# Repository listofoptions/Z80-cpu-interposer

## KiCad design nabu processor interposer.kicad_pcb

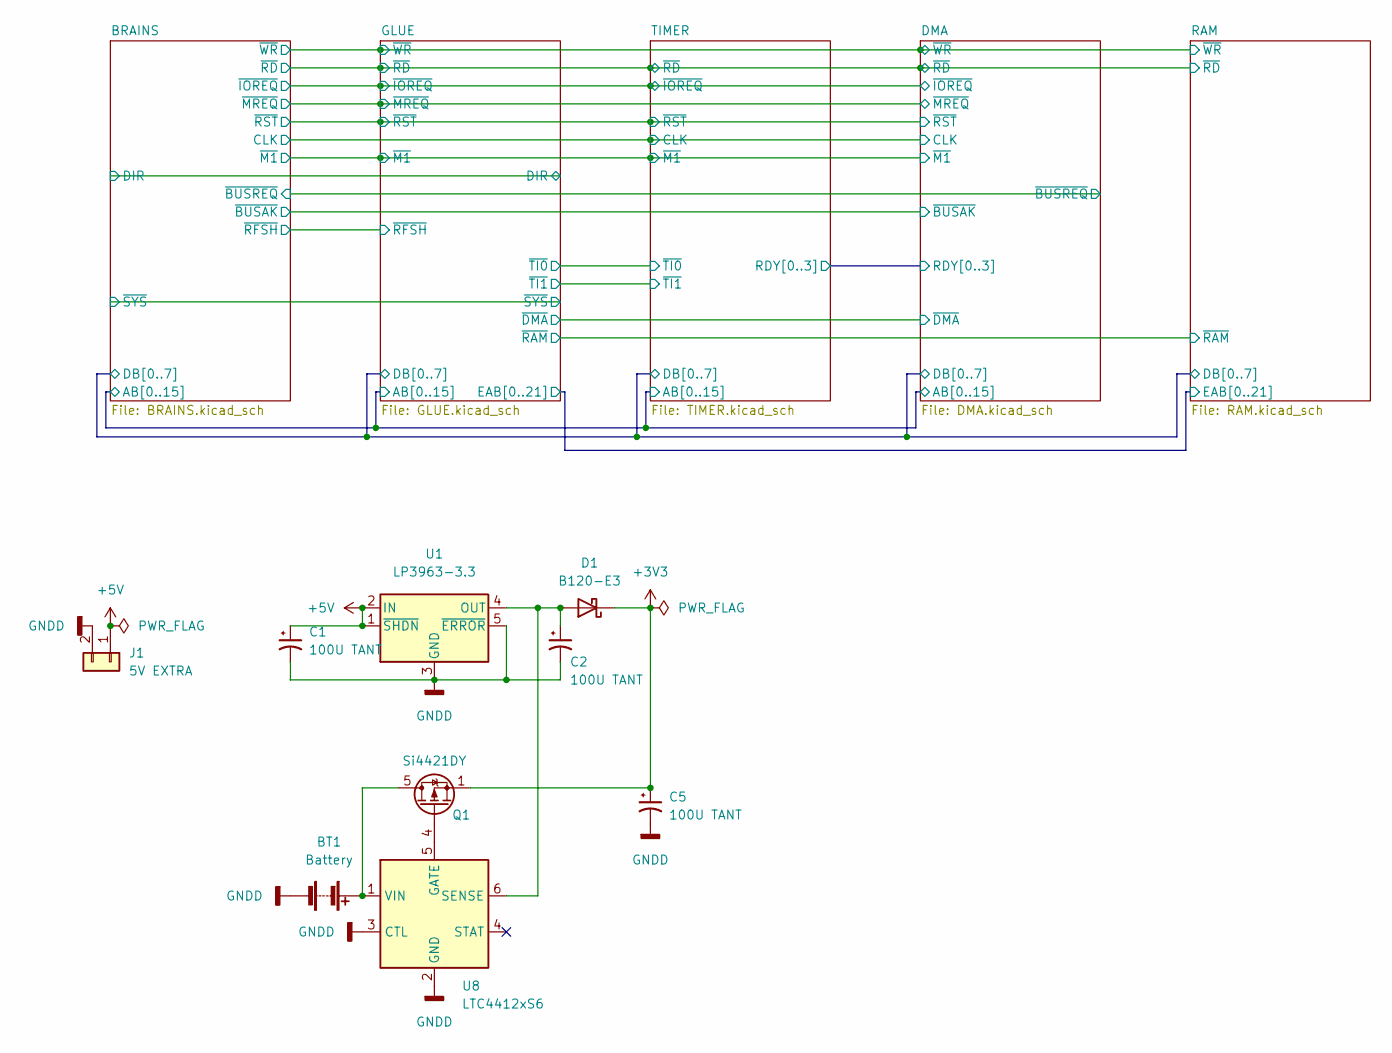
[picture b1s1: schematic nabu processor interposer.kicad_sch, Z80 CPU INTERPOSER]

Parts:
BT1: Battery; BatteryHolder_Keystone_2462_2xAA
C1, C2, C5: 100U TANT; CP_EIA-3528-15_AVX-H
D1: B120-E3; D_SMA
J1: 5V EXTRA; PinHeader_1x02_P2.54mm_Vertical
Q1: Si4421DY; SO-8_3.9x4.9mm_P1.27mm
U1: LP3963-3.3; TO-263-5_TabPin3
U8: LTC4412xS6; TSOT-23-6

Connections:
+3V3: C5.1, D1.1 (K), Q1.1 (S), Q1.2, Q1.3; also elsewhere on the board
+5V: C1.1, J1.1, U1.1 (~SHDN), U1.2 (IN); also elsewhere on the board
GND: BT1.2 (-), C1.2, C2.2, C5.2, J1.2, U1.3 (GND), U1.5 (~ERROR), U8.2 (GND), U8.3 (CTL); also elsewhere on the board
unnamed: BT1.1 (+), Q1.5 (D), Q1.6, Q1.7, Q1.8, U8.1 (VIN)
unnamed: C2.1, D1.2 (A), U1.4 (OUT), U8.6 (SENSE)
unnamed: Q1.4 (G), U8.5 (GATE)

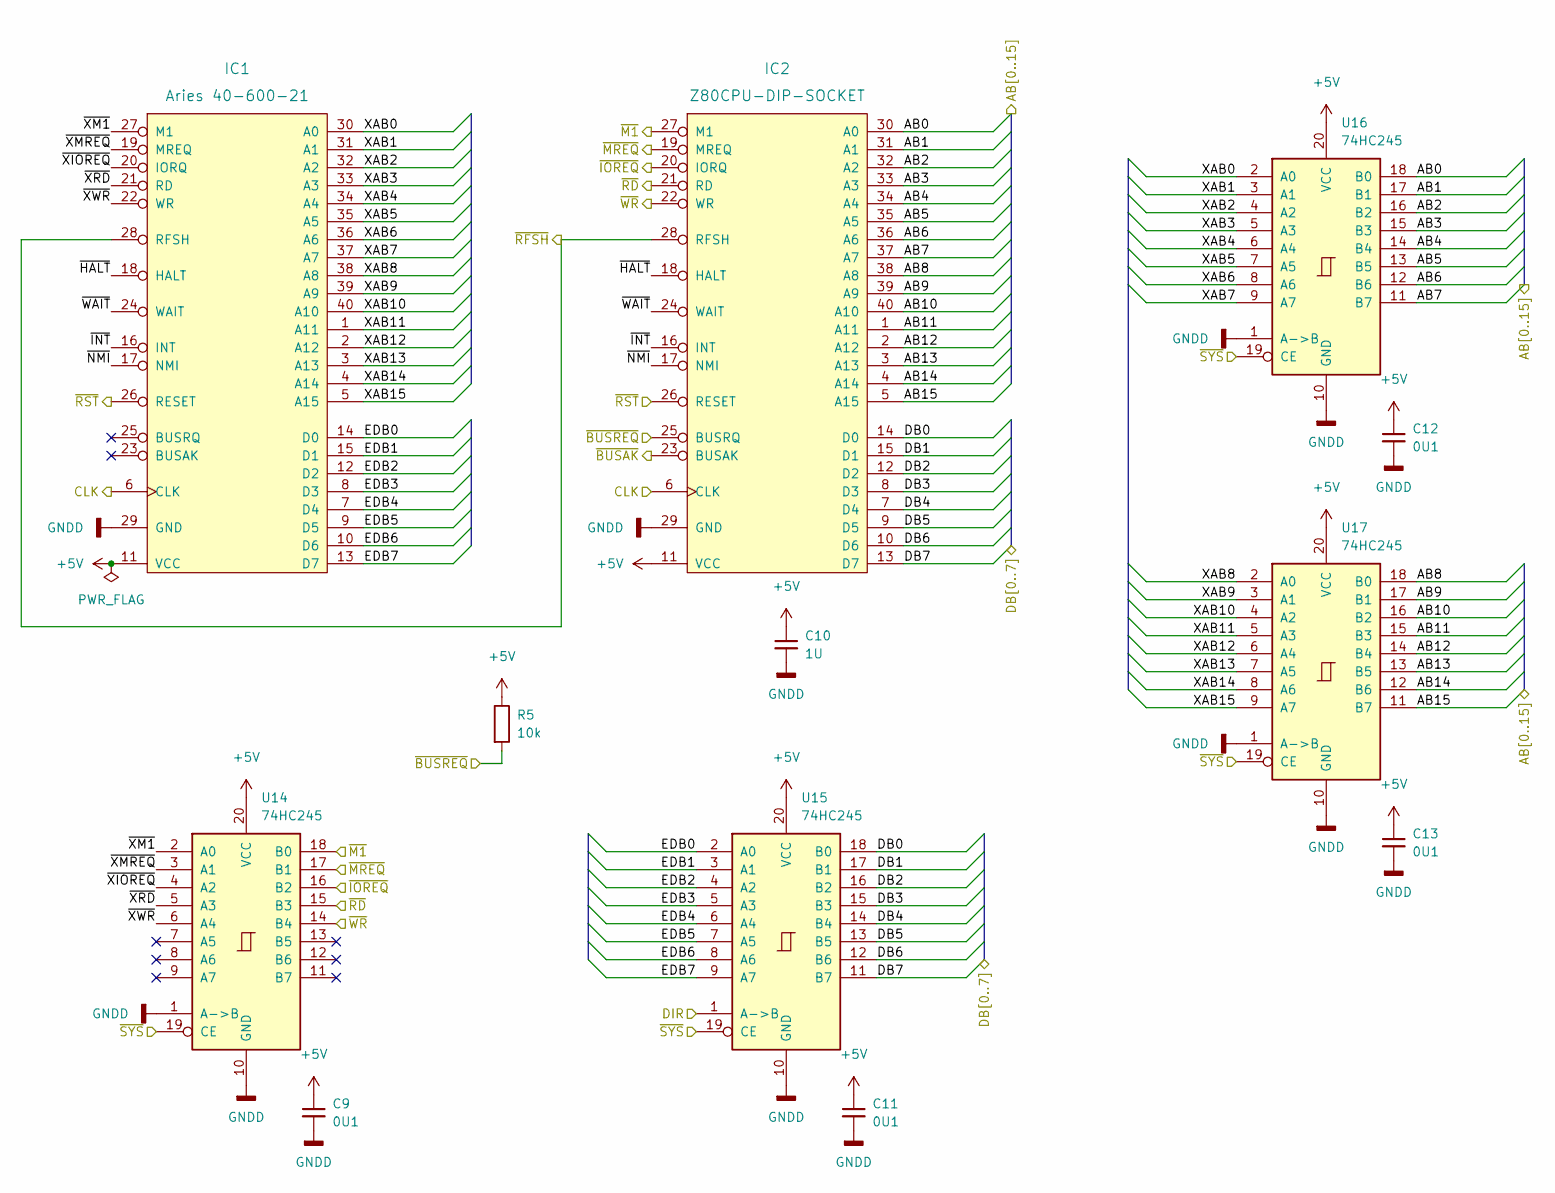
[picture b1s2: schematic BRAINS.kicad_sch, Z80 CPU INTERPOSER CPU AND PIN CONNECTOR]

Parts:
C9, C11, C12, C13: 0U1; C_1206_3216Metric
C10: 1U; C_1206_3216Metric
IC1: Aries 40-600-21; DIP-40_W15.24mm_Socket
IC2: Z80CPU-DIP-SOCKET; DIP-40_W15.24mm_Socket
R5: 10k; R_0603_1608Metric
U14, U15, U16, U17: 74HC245; TSSOP-20_4.4x6.5mm_P0.65mm

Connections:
+5V: C9.1, C10.1, C11.1, C12.1, C13.1, IC1.11 (VCC), IC2.11 (VCC), R5.1, U14.20 (VCC), U15.20 (VCC), U16.20 (VCC), U17.20 (VCC); also elsewhere on the board
/BRAINS/AB0: IC2.30 (A0), U16.18 (B0); also elsewhere on the board
/BRAINS/AB1: IC2.31 (A1), U16.17 (B1); also elsewhere on the board
/BRAINS/AB2: IC2.32 (A2), U16.16 (B2); also elsewhere on the board
/BRAINS/AB3: IC2.33 (A3), U16.15 (B3); also elsewhere on the board
/BRAINS/AB4: IC2.34 (A4), U16.14 (B4); also elsewhere on the board
/BRAINS/AB5: IC2.35 (A5), U16.13 (B5); also elsewhere on the board
/BRAINS/AB6: IC2.36 (A6), U16.12 (B6); also elsewhere on the board
/BRAINS/AB7: IC2.37 (A7), U16.11 (B7); also elsewhere on the board
/BRAINS/AB8: IC2.38 (A8), U17.18 (B0); also elsewhere on the board
/BRAINS/AB9: IC2.39 (A9), U17.17 (B1); also elsewhere on the board
/BRAINS/AB10: IC2.40 (A10), U17.16 (B2); also elsewhere on the board
/BRAINS/AB11: IC2.1 (A11), U17.15 (B3); also elsewhere on the board
/BRAINS/AB12: IC2.2 (A12), U17.14 (B4); also elsewhere on the board
/BRAINS/AB13: IC2.3 (A13), U17.13 (B5); also elsewhere on the board
/BRAINS/AB14: IC2.4 (A14), U17.12 (B6); also elsewhere on the board
/BRAINS/AB15: IC2.5 (A15), U17.11 (B7); also elsewhere on the board
/BRAINS/CLK: IC1.6 (CLK), IC2.6 (CLK); also elsewhere on the board
/BRAINS/DB0: IC2.14 (D0), U15.18 (B0); also elsewhere on the board
/BRAINS/DB1: IC2.15 (D1), U15.17 (B1); also elsewhere on the board
/BRAINS/DB2: IC2.12 (D2), U15.16 (B2); also elsewhere on the board
/BRAINS/DB3: IC2.8 (D3), U15.15 (B3); also elsewhere on the board
/BRAINS/DB4: IC2.7 (D4), U15.14 (B4); also elsewhere on the board
/BRAINS/DB5: IC2.9 (D5), U15.13 (B5); also elsewhere on the board
/BRAINS/DB6: IC2.10 (D6), U15.12 (B6); also elsewhere on the board
/BRAINS/DB7: IC2.13 (D7), U15.11 (B7); also elsewhere on the board
/BRAINS/DIR: U15.1 (A->B); also elsewhere on the board
/BRAINS/EDB0: IC1.14 (D0), U15.2 (A0)
/BRAINS/EDB1: IC1.15 (D1), U15.3 (A1)
/BRAINS/EDB2: IC1.12 (D2), U15.4 (A2)
/BRAINS/EDB3: IC1.8 (D3), U15.5 (A3)
/BRAINS/EDB4: IC1.7 (D4), U15.6 (A4)
/BRAINS/EDB5: IC1.9 (D5), U15.7 (A5)
/BRAINS/EDB6: IC1.10 (D6), U15.8 (A6)
/BRAINS/EDB7: IC1.13 (D7), U15.9 (A7)
/BRAINS/XAB0: IC1.30 (A0), U16.2 (A0)
/BRAINS/XAB1: IC1.31 (A1), U16.3 (A1)
/BRAINS/XAB2: IC1.32 (A2), U16.4 (A2)
/BRAINS/XAB3: IC1.33 (A3), U16.5 (A3)
/BRAINS/XAB4: IC1.34 (A4), U16.6 (A4)
/BRAINS/XAB5: IC1.35 (A5), U16.7 (A5)
/BRAINS/XAB6: IC1.36 (A6), U16.8 (A6)
/BRAINS/XAB7: IC1.37 (A7), U16.9 (A7)
/BRAINS/XAB8: IC1.38 (A8), U17.2 (A0)
/BRAINS/XAB9: IC1.39 (A9), U17.3 (A1)
/BRAINS/XAB10: IC1.40 (A10), U17.4 (A2)
/BRAINS/XAB11: IC1.1 (A11), U17.5 (A3)
/BRAINS/XAB12: IC1.2 (A12), U17.6 (A4)
/BRAINS/XAB13: IC1.3 (A13), U17.7 (A5)
/BRAINS/XAB14: IC1.4 (A14), U17.8 (A6)
/BRAINS/XAB15: IC1.5 (A15), U17.9 (A7)
/BRAINS/~BUSAK: IC2.23 (BUSAK); also elsewhere on the board
/BRAINS/~BUSREQ: IC2.25 (BUSRQ), R5.2; also elsewhere on the board
/BRAINS/~HALT: IC1.18 (HALT), IC2.18 (HALT)
/BRAINS/~INT: IC1.16 (INT), IC2.16 (INT)
/BRAINS/~IOREQ: IC2.20 (IORQ), U14.16 (B2); also elsewhere on the board
/BRAINS/~M1: IC2.27 (M1), U14.18 (B0); also elsewhere on the board
/BRAINS/~MREQ: IC2.19 (MREQ), U14.17 (B1); also elsewhere on the board
/BRAINS/~NMI: IC1.17 (NMI), IC2.17 (NMI)
/BRAINS/~RD: IC2.21 (RD), U14.15 (B3); also elsewhere on the board
/BRAINS/~RFSH: IC1.28 (RFSH), IC2.28 (RFSH); also elsewhere on the board
/BRAINS/~RST: IC1.26 (RESET), IC2.26 (RESET); also elsewhere on the board
/BRAINS/~SYS: U14.19 (CE), U15.19 (CE), U16.19 (CE), U17.19 (CE); also elsewhere on the board
/BRAINS/~WAIT: IC1.24 (WAIT), IC2.24 (WAIT)
/BRAINS/~WR: IC2.22 (WR), U14.14 (B4); also elsewhere on the board
/BRAINS/~XIOREQ: IC1.20 (IORQ), U14.4 (A2)
/BRAINS/~XM1: IC1.27 (M1), U14.2 (A0)
/BRAINS/~XMREQ: IC1.19 (MREQ), U14.3 (A1)
/BRAINS/~XRD: IC1.21 (RD), U14.5 (A3)
/BRAINS/~XWR: IC1.22 (WR), U14.6 (A4)
GND: C9.2, C10.2, C11.2, C12.2, C13.2, IC1.29 (GND), IC2.29 (GND), U14.1 (A->B), U14.10 (GND), U15.10 (GND), U16.1 (A->B), U16.10 (GND), U17.1 (A->B), U17.10 (GND); also elsewhere on the board

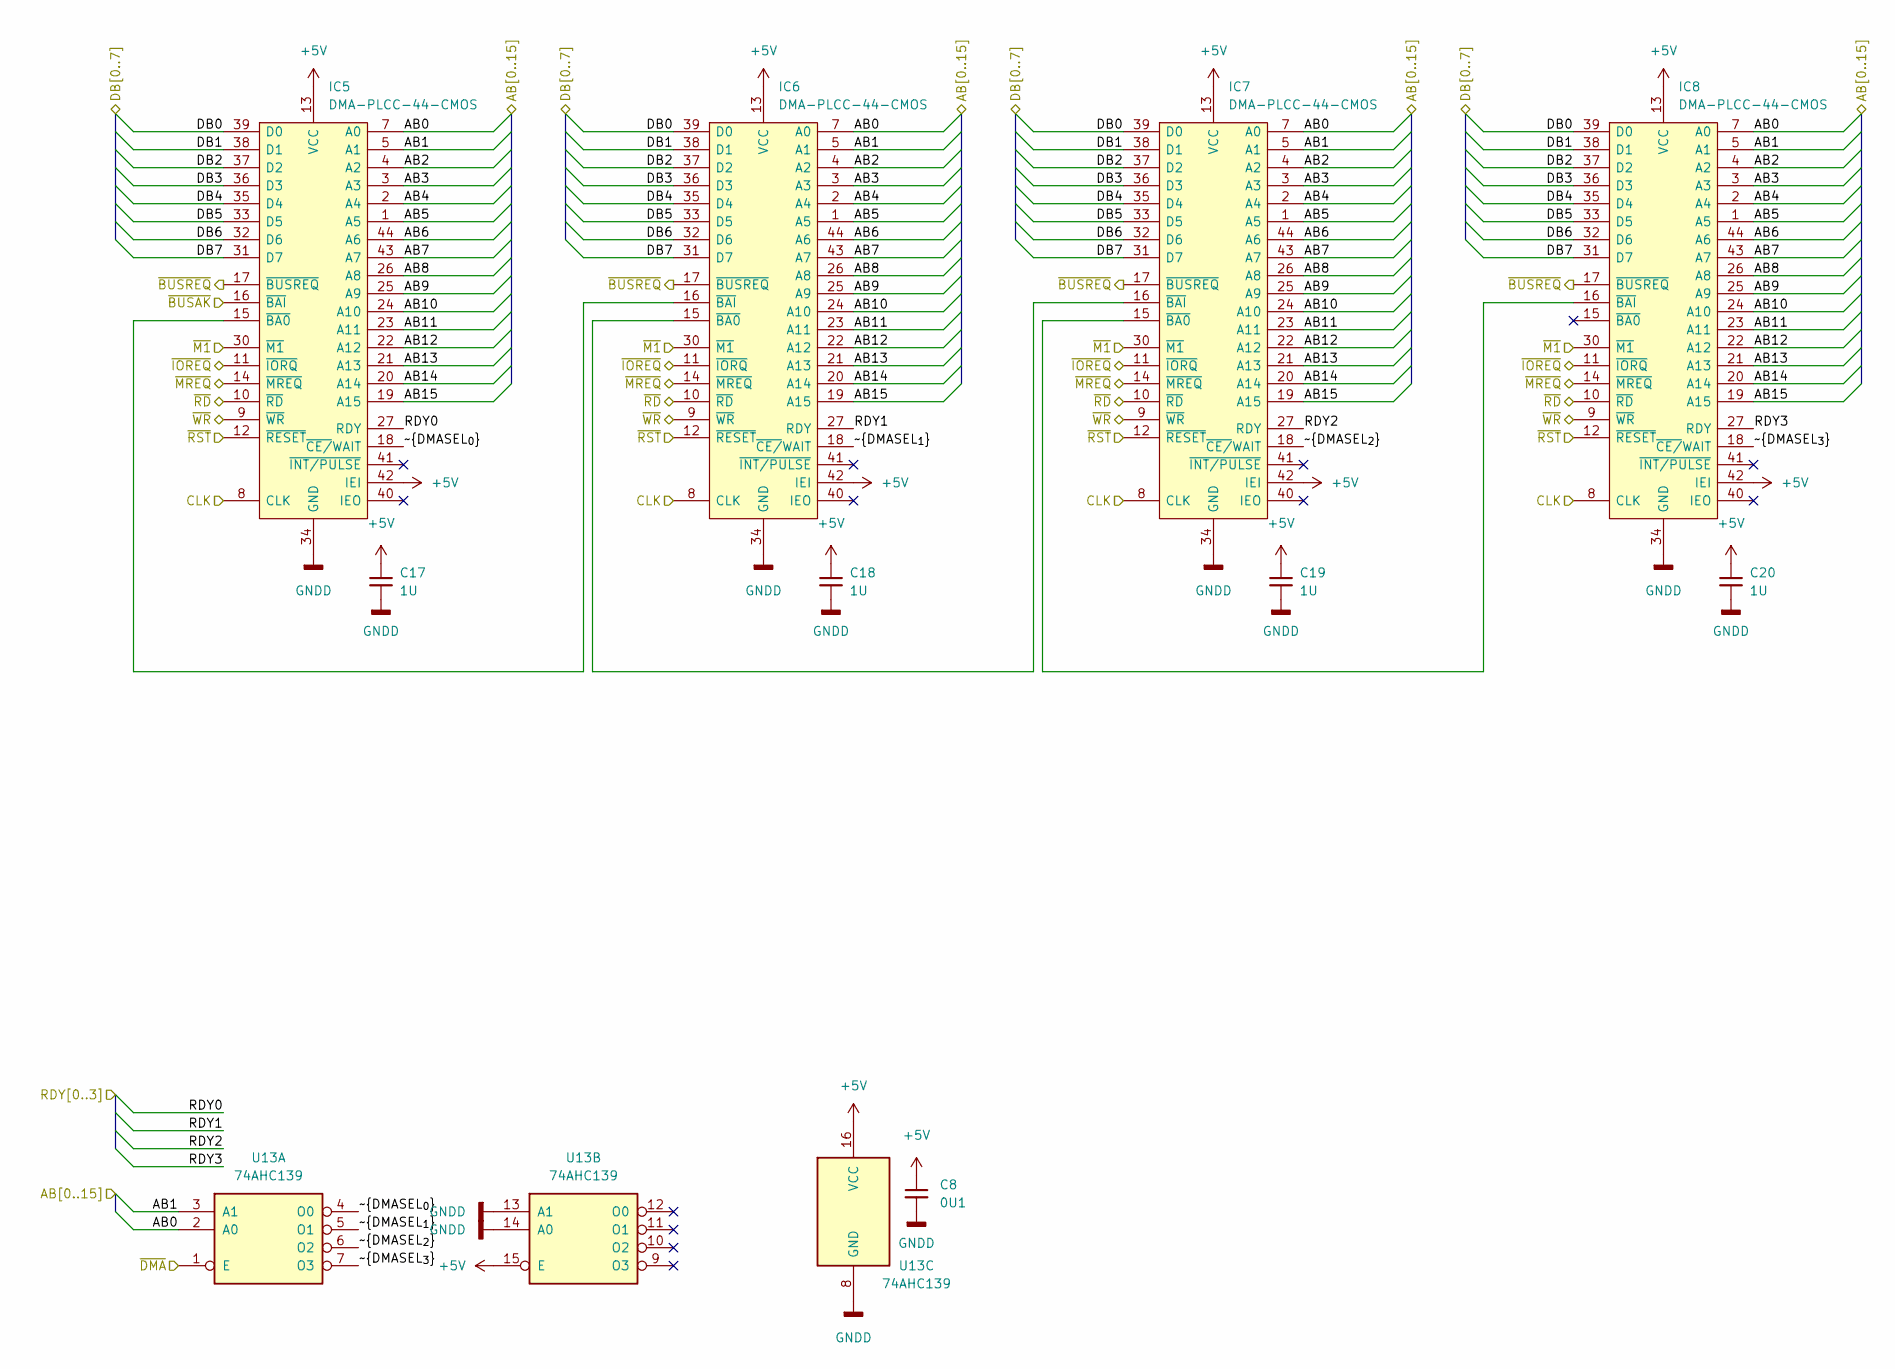
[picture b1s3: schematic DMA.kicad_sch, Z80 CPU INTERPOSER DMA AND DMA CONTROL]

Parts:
C8: 0U1; C_0603_1608Metric
C17, C18, C19, C20: 1U; C_1206_3216Metric
IC5, IC6, IC7, IC8: DMA-PLCC-44-CMOS; LQFP-44_10x10mm_P0.8mm; Manufacturer_Part_Number Z84C4206PEG; Mouser Part Number 692-Z84C4206PEG
U13: 74AHC139; TSSOP-16_4.4x5mm_P0.65mm

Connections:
+5V: C8.1, C17.1, C18.1, C19.1, C20.1, IC5.13 (VCC), IC5.42 (IEI), IC6.13 (VCC), IC6.42 (IEI), IC7.13 (VCC), IC7.42 (IEI), IC8.13 (VCC), IC8.42 (IEI), U13.15 (E), U13.16 (VCC); also elsewhere on the board
/BRAINS/AB0: IC5.7 (A0), IC6.7 (A0), IC7.7 (A0), IC8.7 (A0), U13.2 (A0); also elsewhere on the board
/BRAINS/AB1: IC5.5 (A1), IC6.5 (A1), IC7.5 (A1), IC8.5 (A1), U13.3 (A1); also elsewhere on the board
/BRAINS/AB2: IC5.4 (A2), IC6.4 (A2), IC7.4 (A2), IC8.4 (A2); also elsewhere on the board
/BRAINS/AB3: IC5.3 (A3), IC6.3 (A3), IC7.3 (A3), IC8.3 (A3); also elsewhere on the board
/BRAINS/AB4: IC5.2 (A4), IC6.2 (A4), IC7.2 (A4), IC8.2 (A4); also elsewhere on the board
/BRAINS/AB5: IC5.1 (A5), IC6.1 (A5), IC7.1 (A5), IC8.1 (A5); also elsewhere on the board
/BRAINS/AB6: IC5.44 (A6), IC6.44 (A6), IC7.44 (A6), IC8.44 (A6); also elsewhere on the board
/BRAINS/AB7: IC5.43 (A7), IC6.43 (A7), IC7.43 (A7), IC8.43 (A7); also elsewhere on the board
/BRAINS/AB8: IC5.26 (A8), IC6.26 (A8), IC7.26 (A8), IC8.26 (A8); also elsewhere on the board
/BRAINS/AB9: IC5.25 (A9), IC6.25 (A9), IC7.25 (A9), IC8.25 (A9); also elsewhere on the board
/BRAINS/AB10: IC5.24 (A10), IC6.24 (A10), IC7.24 (A10), IC8.24 (A10); also elsewhere on the board
/BRAINS/AB11: IC5.23 (A11), IC6.23 (A11), IC7.23 (A11), IC8.23 (A11); also elsewhere on the board
/BRAINS/AB12: IC5.22 (A12), IC6.22 (A12), IC7.22 (A12), IC8.22 (A12); also elsewhere on the board
/BRAINS/AB13: IC5.21 (A13), IC6.21 (A13), IC7.21 (A13), IC8.21 (A13); also elsewhere on the board
/BRAINS/AB14: IC5.20 (A14), IC6.20 (A14), IC7.20 (A14), IC8.20 (A14); also elsewhere on the board
/BRAINS/AB15: IC5.19 (A15), IC6.19 (A15), IC7.19 (A15), IC8.19 (A15); also elsewhere on the board
/BRAINS/CLK: IC5.8 (CLK), IC6.8 (CLK), IC7.8 (CLK), IC8.8 (CLK); also elsewhere on the board
/BRAINS/DB0: IC5.39 (D0), IC6.39 (D0), IC7.39 (D0), IC8.39 (D0); also elsewhere on the board
/BRAINS/DB1: IC5.38 (D1), IC6.38 (D1), IC7.38 (D1), IC8.38 (D1); also elsewhere on the board
/BRAINS/DB2: IC5.37 (D2), IC6.37 (D2), IC7.37 (D2), IC8.37 (D2); also elsewhere on the board
/BRAINS/DB3: IC5.36 (D3), IC6.36 (D3), IC7.36 (D3), IC8.36 (D3); also elsewhere on the board
/BRAINS/DB4: IC5.35 (D4), IC6.35 (D4), IC7.35 (D4), IC8.35 (D4); also elsewhere on the board
/BRAINS/DB5: IC5.33 (D5), IC6.33 (D5), IC7.33 (D5), IC8.33 (D5); also elsewhere on the board
/BRAINS/DB6: IC5.32 (D6), IC6.32 (D6), IC7.32 (D6), IC8.32 (D6); also elsewhere on the board
/BRAINS/DB7: IC5.31 (D7), IC6.31 (D7), IC7.31 (D7), IC8.31 (D7); also elsewhere on the board
/BRAINS/~BUSAK: IC5.16 (~BAI); also elsewhere on the board
/BRAINS/~BUSREQ: IC5.17 (~BUSREQ), IC6.17 (~BUSREQ), IC7.17 (~BUSREQ), IC8.17 (~BUSREQ); also elsewhere on the board
/BRAINS/~IOREQ: IC5.11 (~IORQ), IC6.11 (~IORQ), IC7.11 (~IORQ), IC8.11 (~IORQ); also elsewhere on the board
/BRAINS/~M1: IC5.30 (~M1), IC6.30 (~M1), IC7.30 (~M1), IC8.30 (~M1); also elsewhere on the board
/BRAINS/~MREQ: IC5.14 (~MREQ), IC6.14 (~MREQ), IC7.14 (~MREQ), IC8.14 (~MREQ); also elsewhere on the board
/BRAINS/~RD: IC5.10 (~RD), IC6.10 (~RD), IC7.10 (~RD), IC8.10 (~RD); also elsewhere on the board
/BRAINS/~RST: IC5.12 (~RESET), IC6.12 (~RESET), IC7.12 (~RESET), IC8.12 (~RESET); also elsewhere on the board
/BRAINS/~WR: IC5.9 (~WR), IC6.9 (~WR), IC7.9 (~WR), IC8.9 (~WR); also elsewhere on the board
/DMA/RDY0: IC5.27 (RDY); also elsewhere on the board
/DMA/RDY1: IC6.27 (RDY); also elsewhere on the board
/DMA/RDY2: IC7.27 (RDY); also elsewhere on the board
/DMA/RDY3: IC8.27 (RDY); also elsewhere on the board
/DMA/~DMASEL_{0}: IC5.18 (~CE/WAIT), U13.4 (O0)
/DMA/~DMASEL_{1}: IC6.18 (~CE/WAIT), U13.5 (O1)
/DMA/~DMASEL_{2}: IC7.18 (~CE/WAIT), U13.6 (O2)
/DMA/~DMASEL_{3}: IC8.18 (~CE/WAIT), U13.7 (O3)
/DMA/~DMA: U13.1 (E); also elsewhere on the board
GND: C8.2, C17.2, C18.2, C19.2, C20.2, IC5.34 (GND), IC6.34 (GND), IC7.34 (GND), IC8.34 (GND), U13.8 (GND), U13.13 (A1), U13.14 (A0); also elsewhere on the board
unnamed: IC5.15 (~BA0), IC6.16 (~BAI)
unnamed: IC6.15 (~BA0), IC7.16 (~BAI)
unnamed: IC7.15 (~BA0), IC8.16 (~BAI)

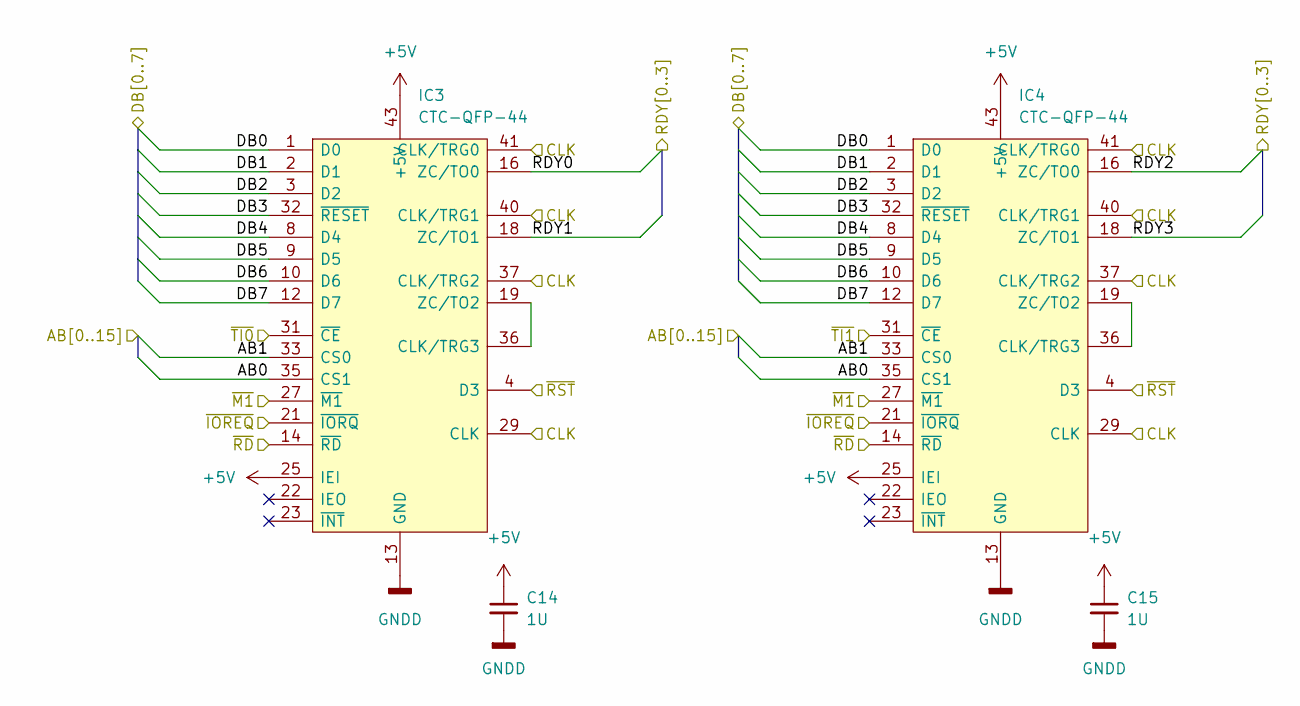
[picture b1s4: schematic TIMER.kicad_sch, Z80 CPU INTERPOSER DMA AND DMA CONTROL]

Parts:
C14, C15: 1U; C_1206_3216Metric
IC3, IC4: CTC-QFP-44; LQFP-44_10x10mm_P0.8mm; Manufacturer_Part_Number Z84C3010PEG; Mouser Part Number 692-Z84C3010PEG

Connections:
+5V: C14.1, C15.1, IC3.25 (IEI), IC3.43 (+5V), IC4.25 (IEI), IC4.43 (+5V); also elsewhere on the board
/BRAINS/AB0: IC3.35 (CS1), IC4.35 (CS1); also elsewhere on the board
/BRAINS/AB1: IC3.33 (CS0), IC4.33 (CS0); also elsewhere on the board
/BRAINS/CLK: IC3.29 (CLK), IC3.37 (CLK/TRG2), IC3.40 (CLK/TRG1), IC3.41 (CLK/TRG0), IC4.29 (CLK), IC4.37 (CLK/TRG2), IC4.40 (CLK/TRG1), IC4.41 (CLK/TRG0); also elsewhere on the board
/BRAINS/DB0: IC3.1 (D0), IC4.1 (D0); also elsewhere on the board
/BRAINS/DB1: IC3.2 (D1), IC4.2 (D1); also elsewhere on the board
/BRAINS/DB2: IC3.3 (D2), IC4.3 (D2); also elsewhere on the board
/BRAINS/DB3: IC3.32 (~RESET), IC4.32 (~RESET); also elsewhere on the board
/BRAINS/DB4: IC3.8 (D4), IC4.8 (D4); also elsewhere on the board
/BRAINS/DB5: IC3.9 (D5), IC4.9 (D5); also elsewhere on the board
/BRAINS/DB6: IC3.10 (D6), IC4.10 (D6); also elsewhere on the board
/BRAINS/DB7: IC3.12 (D7), IC4.12 (D7); also elsewhere on the board
/BRAINS/~IOREQ: IC3.21 (~IORQ), IC4.21 (~IORQ); also elsewhere on the board
/BRAINS/~M1: IC3.27 (~M1), IC4.27 (~M1); also elsewhere on the board
/BRAINS/~RD: IC3.14 (~RD), IC4.14 (~RD); also elsewhere on the board
/BRAINS/~RST: IC3.4 (D3), IC4.4 (D3); also elsewhere on the board
/DMA/RDY0: IC3.16 (ZC/TO0); also elsewhere on the board
/DMA/RDY1: IC3.18 (ZC/TO1); also elsewhere on the board
/DMA/RDY2: IC4.16 (ZC/TO0); also elsewhere on the board
/DMA/RDY3: IC4.18 (ZC/TO1); also elsewhere on the board
/GLUE/~TI0: IC3.31 (~CE); also elsewhere on the board
/GLUE/~TI1: IC4.31 (~CE); also elsewhere on the board
GND: C14.2, C15.2, IC3.13 (GND), IC4.13 (GND); also elsewhere on the board
unnamed: IC3.19 (ZC/TO2), IC3.36 (CLK/TRG3)
unnamed: IC4.19 (ZC/TO2), IC4.36 (CLK/TRG3)

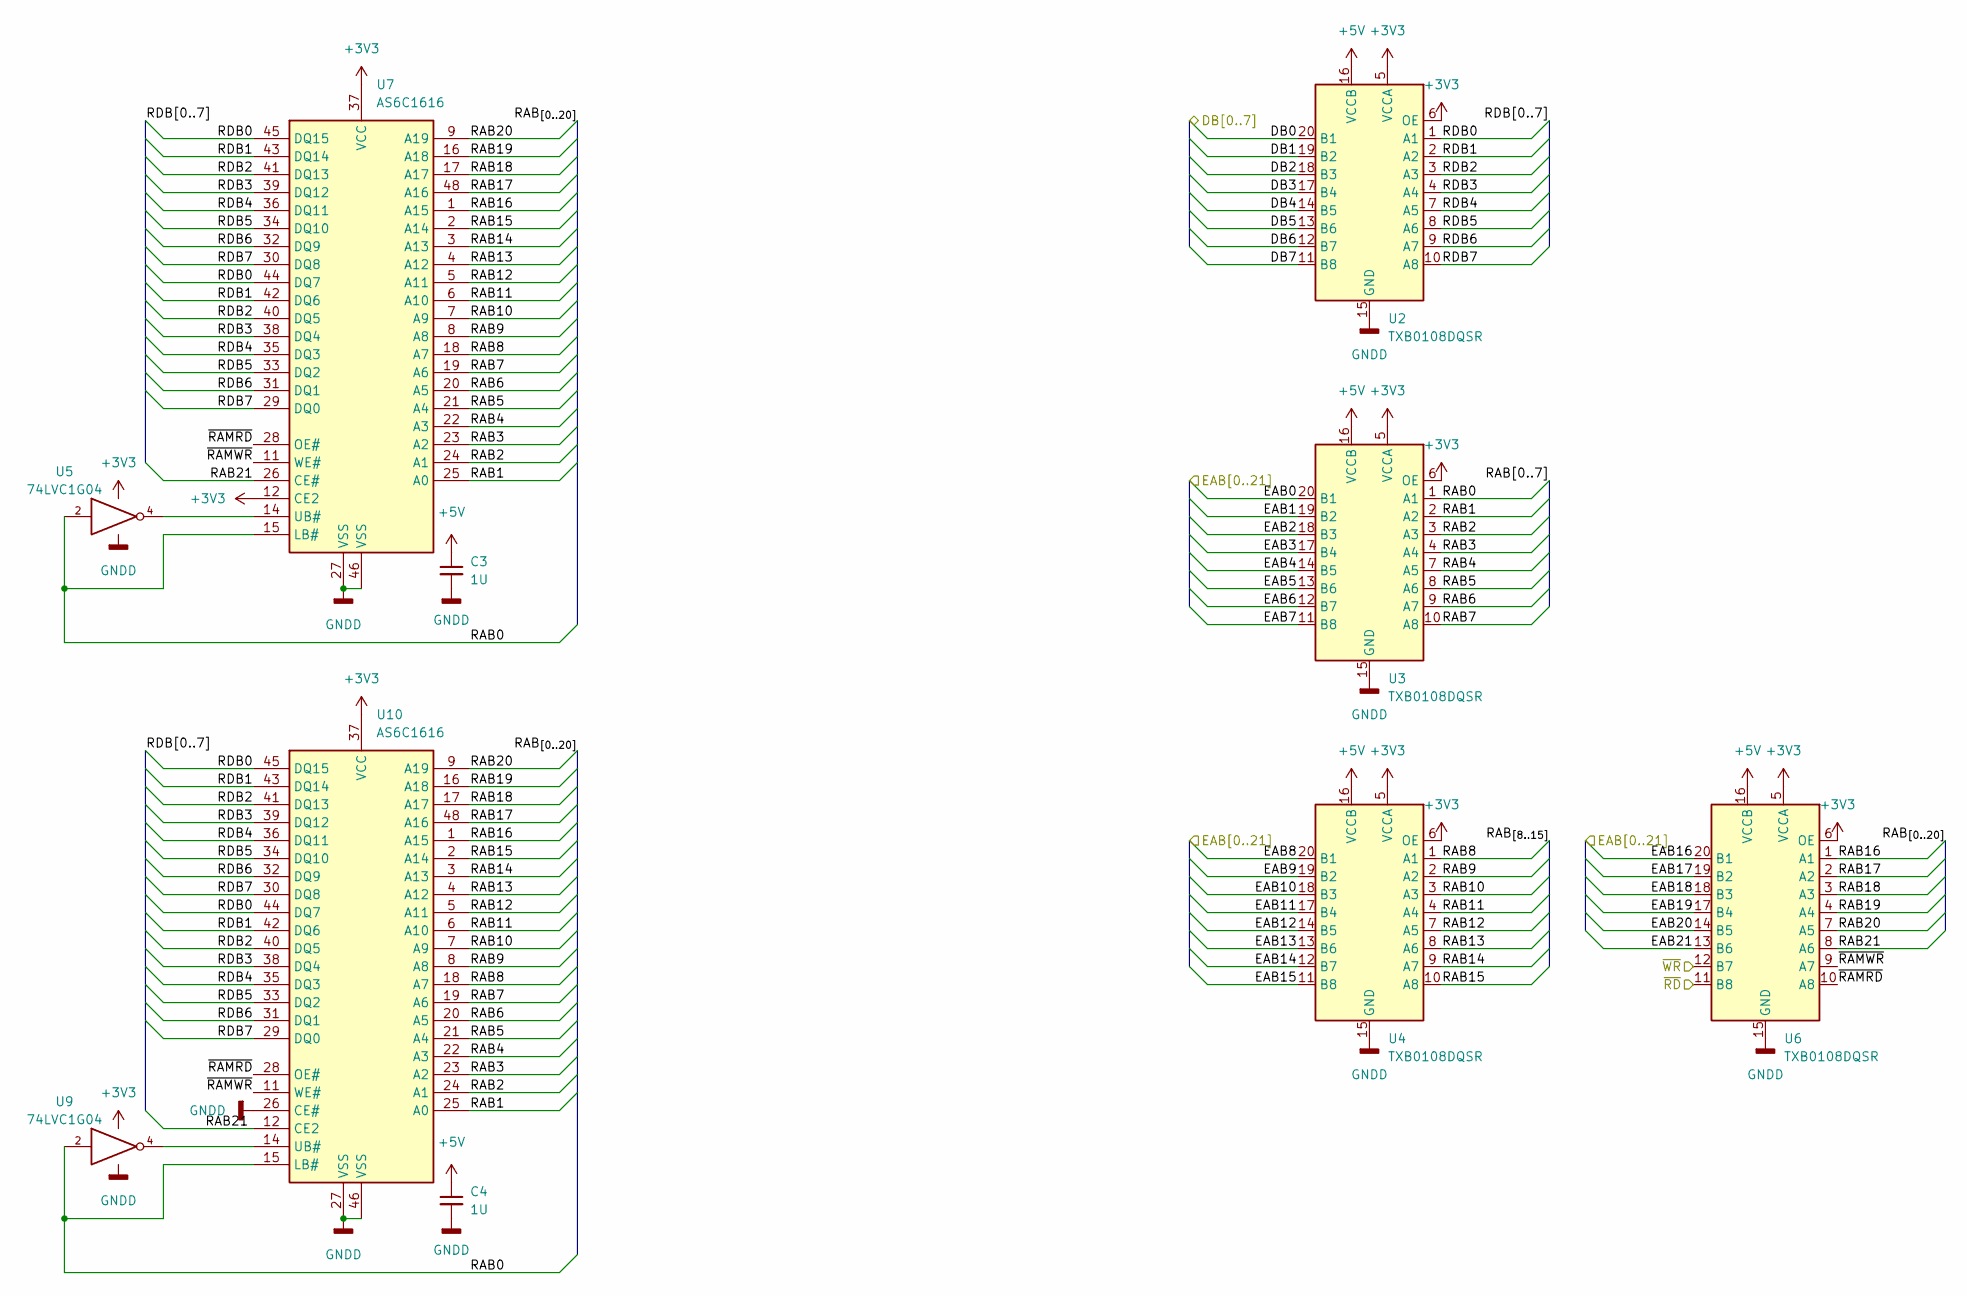
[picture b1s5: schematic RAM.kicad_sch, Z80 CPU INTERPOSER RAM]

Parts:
C3, C4: 1U; C_1206_3216Metric
U2, U3, U4, U6: TXB0108DQSR; USON-20_2x4mm_P0.4mm
U5, U9: 74LVC1G04; SOT-353_SC-70-5
U7, U10: AS6C1616; TSOP-I-48_18.4x12mm_P0.5mm

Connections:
+3V3: U2.5 (VCCA), U2.6 (OE), U3.5 (VCCA), U3.6 (OE), U4.5 (VCCA), U4.6 (OE), U5.5 (VCC), U6.5 (VCCA), U6.6 (OE), U7.12 (CE2), U7.37 (VCC), U9.5 (VCC), U10.37 (VCC); also elsewhere on the board
+5V: C3.1, C4.1, U2.16 (VCCB), U3.16 (VCCB), U4.16 (VCCB), U6.16 (VCCB); also elsewhere on the board
/BRAINS/AB0: U3.20 (B1); also elsewhere on the board
/BRAINS/AB1: U3.19 (B2); also elsewhere on the board
/BRAINS/AB2: U3.18 (B3); also elsewhere on the board
/BRAINS/AB3: U3.17 (B4); also elsewhere on the board
/BRAINS/AB4: U3.14 (B5); also elsewhere on the board
/BRAINS/AB5: U3.13 (B6); also elsewhere on the board
/BRAINS/AB6: U3.12 (B7); also elsewhere on the board
/BRAINS/AB7: U3.11 (B8); also elsewhere on the board
/BRAINS/AB8: U4.20 (B1); also elsewhere on the board
/BRAINS/AB9: U4.19 (B2); also elsewhere on the board
/BRAINS/AB10: U4.18 (B3); also elsewhere on the board
/BRAINS/AB11: U4.17 (B4); also elsewhere on the board
/BRAINS/AB12: U4.14 (B5); also elsewhere on the board
/BRAINS/AB13: U4.13 (B6); also elsewhere on the board
/BRAINS/DB0: U2.20 (B1); also elsewhere on the board
/BRAINS/DB1: U2.19 (B2); also elsewhere on the board
/BRAINS/DB2: U2.18 (B3); also elsewhere on the board
/BRAINS/DB3: U2.17 (B4); also elsewhere on the board
/BRAINS/DB4: U2.14 (B5); also elsewhere on the board
/BRAINS/DB5: U2.13 (B6); also elsewhere on the board
/BRAINS/DB6: U2.12 (B7); also elsewhere on the board
/BRAINS/DB7: U2.11 (B8); also elsewhere on the board
/BRAINS/~RD: U6.11 (B8); also elsewhere on the board
/BRAINS/~WR: U6.12 (B7); also elsewhere on the board
/GLUE/EAB14: U4.12 (B7); also elsewhere on the board
/GLUE/EAB15: U4.11 (B8); also elsewhere on the board
/GLUE/EAB16: U6.20 (B1); also elsewhere on the board
/GLUE/EAB17: U6.19 (B2); also elsewhere on the board
/GLUE/EAB18: U6.18 (B3); also elsewhere on the board
/GLUE/EAB19: U6.17 (B4); also elsewhere on the board
/GLUE/EAB20: U6.14 (B5); also elsewhere on the board
/GLUE/EAB21: U6.13 (B6); also elsewhere on the board
/RAM/RAB0: U3.1 (A1), U5.2, U7.15 (LB#), U9.2, U10.15 (LB#)
/RAM/RAB1: U3.2 (A2), U7.25 (A0), U10.25 (A0)
/RAM/RAB2: U3.3 (A3), U7.24 (A1), U10.24 (A1)
/RAM/RAB3: U3.4 (A4), U7.23 (A2), U10.23 (A2)
/RAM/RAB4: U3.7 (A5), U7.22 (A3), U10.22 (A3)
/RAM/RAB5: U3.8 (A6), U7.21 (A4), U10.21 (A4)
/RAM/RAB6: U3.9 (A7), U7.20 (A5), U10.20 (A5)
/RAM/RAB7: U3.10 (A8), U7.19 (A6), U10.19 (A6)
/RAM/RAB8: U4.1 (A1), U7.18 (A7), U10.18 (A7)
/RAM/RAB9: U4.2 (A2), U7.8 (A8), U10.8 (A8)
/RAM/RAB10: U4.3 (A3), U7.7 (A9), U10.7 (A9)
/RAM/RAB11: U4.4 (A4), U7.6 (A10), U10.6 (A10)
/RAM/RAB12: U4.7 (A5), U7.5 (A11), U10.5 (A11)
/RAM/RAB13: U4.8 (A6), U7.4 (A12), U10.4 (A12)
/RAM/RAB14: U4.9 (A7), U7.3 (A13), U10.3 (A13)
/RAM/RAB15: U4.10 (A8), U7.2 (A14), U10.2 (A14)
/RAM/RAB16: U6.1 (A1), U7.1 (A15), U10.1 (A15)
/RAM/RAB17: U6.2 (A2), U7.48 (A16), U10.48 (A16)
/RAM/RAB18: U6.3 (A3), U7.17 (A17), U10.17 (A17)
/RAM/RAB19: U6.4 (A4), U7.16 (A18), U10.16 (A18)
/RAM/RAB20: U6.7 (A5), U7.9 (A19), U10.9 (A19)
/RAM/RAB21: U6.8 (A6), U7.26 (CE#), U10.12 (CE2)
/RAM/RDB0: U2.1 (A1), U7.44 (DQ7), U7.45 (DQ15), U10.44 (DQ7), U10.45 (DQ15)
/RAM/RDB1: U2.2 (A2), U7.42 (DQ6), U7.43 (DQ14), U10.42 (DQ6), U10.43 (DQ14)
/RAM/RDB2: U2.3 (A3), U7.40 (DQ5), U7.41 (DQ13), U10.40 (DQ5), U10.41 (DQ13)
/RAM/RDB3: U2.4 (A4), U7.38 (DQ4), U7.39 (DQ12), U10.38 (DQ4), U10.39 (DQ12)
/RAM/RDB4: U2.7 (A5), U7.35 (DQ3), U7.36 (DQ11), U10.35 (DQ3), U10.36 (DQ11)
/RAM/RDB5: U2.8 (A6), U7.33 (DQ2), U7.34 (DQ10), U10.33 (DQ2), U10.34 (DQ10)
/RAM/RDB6: U2.9 (A7), U7.31 (DQ1), U7.32 (DQ9), U10.31 (DQ1), U10.32 (DQ9)
/RAM/RDB7: U2.10 (A8), U7.29 (DQ0), U7.30 (DQ8), U10.29 (DQ0), U10.30 (DQ8)
/RAM/~RAMRD: U6.10 (A8), U7.28 (OE#), U10.28 (OE#)
/RAM/~RAMWR: U6.9 (A7), U7.11 (WE#), U10.11 (WE#)
GND: C3.2, C4.2, U2.15 (GND), U3.15 (GND), U4.15 (GND), U5.3 (GND), U6.15 (GND), U7.27 (VSS), U7.46 (VSS), U9.3 (GND), U10.26 (CE#), U10.27 (VSS), U10.46 (VSS); also elsewhere on the board
unnamed: U5.4, U7.14 (UB#)
unnamed: U9.4, U10.14 (UB#)
